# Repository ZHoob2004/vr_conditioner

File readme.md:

# vr_conditioner

__In hingsight, this was a poor choice of chip, and this didn't work - see [mck1117/vr-interface](github.com/mck1117/vr-interface) for working design__

~~VR conditioner board for Honda OBD0, OBD1, and early OBD2 VR sensors~~

~~Based (heavily) on https://rusefi.com/forum/viewtopic.php?f=3&t=1115&p=20857&hilit=honda#p20862~~

~~Rerouted as 2-layer board and reduced PCB area by more than 50%.~~

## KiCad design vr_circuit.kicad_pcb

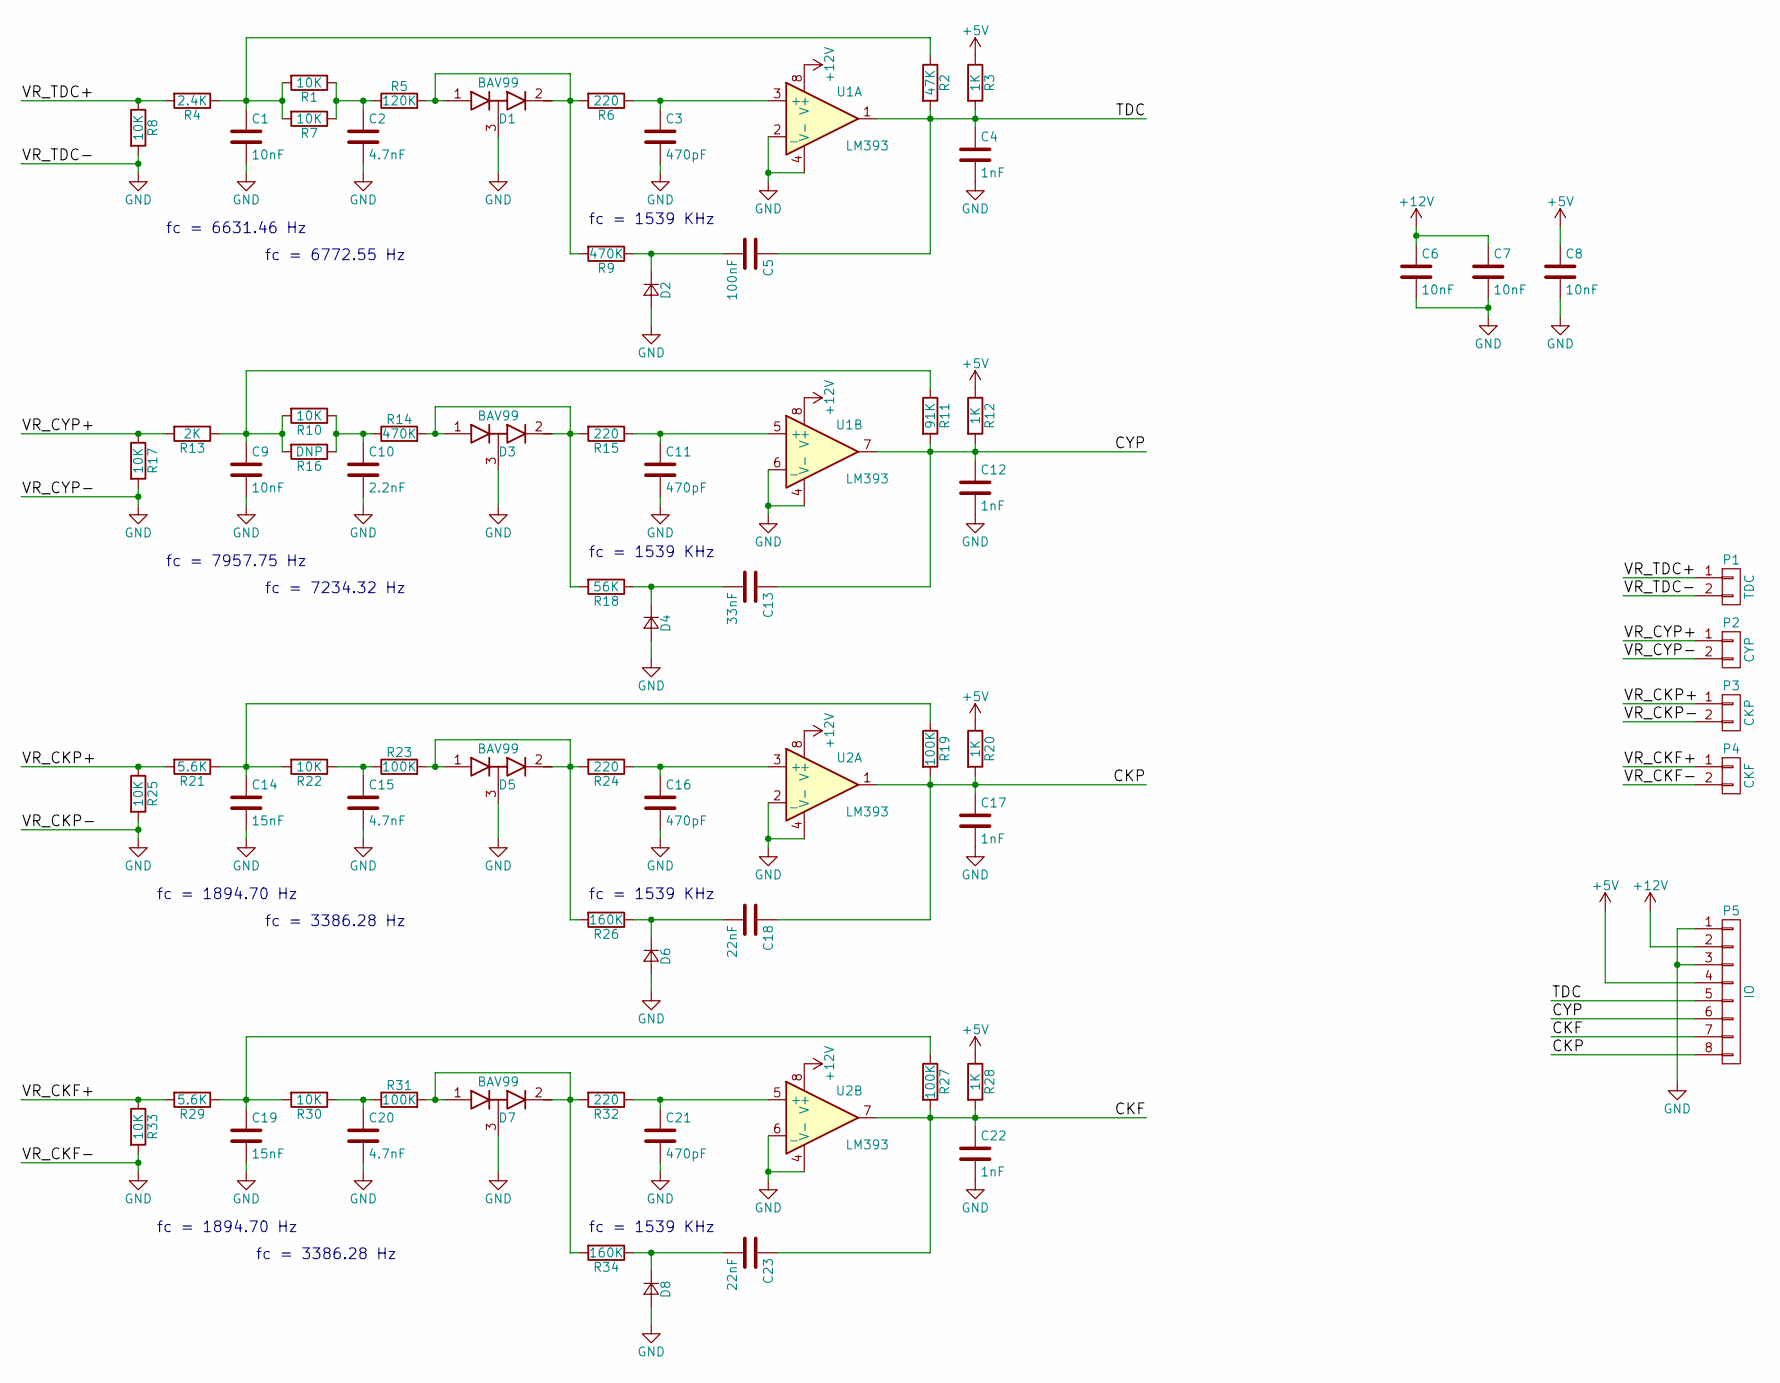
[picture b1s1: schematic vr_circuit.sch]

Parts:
C1, C6, C7, C8, C9: 10nF; C_0805_HandSoldering
C2, C15, C20: 4.7nF; C_0805_HandSoldering
C3, C11, C16, C21: 470pF; C_0805_HandSoldering
C4, C12, C17, C22: 1nF; C_0805_HandSoldering
C5: 100nF; C_1206_HandSoldering
C10: 2.2nF; C_0805_HandSoldering
C13: 33nF; C_1206_HandSoldering
C14, C19: 15nF; C_0805_HandSoldering
C18, C23: 22nF; C_1206_HandSoldering
D1, D3, D5, D7: BAV99; SOT-23_Handsoldering
D2, D4, D6, D8: D_Small; SOD-523
P1: TDC; Pin_Header_Straight_1x02
P2: CYP; Pin_Header_Straight_1x02
P3: CKP; Pin_Header_Straight_1x02
P4: CKF; Pin_Header_Straight_1x02
P5: IO; Pin_Header_Straight_1x08
R1, R7, R10, R22, R30: 10K; R_0805_HandSoldering
R2: 47K; R_0805_HandSoldering
R3, R12, R20, R28: 1K; R_0805_HandSoldering
R4: 2.4K; R_0805_HandSoldering
R5: 120K; R_0805_HandSoldering
R6, R15, R24, R32: 220; R_0805_HandSoldering
R8, R17, R25, R33: 10K; R_2512_HandSoldering
R9, R14: 470K; R_0805_HandSoldering
R11: 91K; R_0805_HandSoldering
R13: 2K; R_0805_HandSoldering
R16: DNP; R_0805_HandSoldering
R18: 56K; R_0805_HandSoldering
R19, R23, R27, R31: 100K; R_0805_HandSoldering
R21, R29: 5.6K; R_0805_HandSoldering
R26, R34: 160K; R_0805_HandSoldering
U1, U2: LM393; SOIC-8-N

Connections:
+5V: C8.1, P5.4, R3.1, R12.1, R20.1, R28.1
+12V: C6.1, C7.1, P5.2, U1.8 (V+), U2.8 (V+)
/CKF: C22.1, C23.1, P5.7, R27.2, R28.2, U2.7
/CKP: C17.1, C18.1, P5.8, R19.2, R20.2, U2.1
/CYP: C12.1, C13.1, P5.6, R11.2, R12.2, U1.7
/TDC: C4.1, C5.1, P5.5, R2.2, R3.2, U1.1
/VR_CKF+: P4.1, R29.2, R33.1
/VR_CKP+: P3.1, R21.2, R25.1
/VR_CYP+: P2.1, R13.2, R17.1
/VR_TDC+: P1.1, R4.2, R8.1
GND: C1.2, C2.2, C3.2, C4.2, C6.2, C7.2, C8.2, C9.2, C10.2, C11.2, C12.2, C14.2, C15.2, C16.2, C17.2, C19.2, C20.2, C21.2, C22.2, D1.3 (common), D2.2 (A), D3.3 (common), D4.2 (A), D5.3 (common), D6.2 (A), D7.3 (common), D8.2 (A), P1.2, P2.2, P3.2, P4.2, P5.1, P5.3, R8.2, R17.2, R25.2, R33.2, U1.2 (_), U1.4 (V-), U1.6 (_), U2.2 (_), U2.4 (V-), U2.6 (_)
unnamed: C1.1, R1.2, R2.1, R4.1, R7.2
unnamed: C2.1, R1.1, R5.1, R7.1
unnamed: C3.1, R6.1, U1.3 (+)
unnamed: C5.2, D2.1 (K), R9.1
unnamed: C9.1, R10.2, R11.1, R13.1, R16.2
unnamed: C10.1, R10.1, R14.1, R16.1
unnamed: C11.1, R15.1, U1.5 (+)
unnamed: C13.2, D4.1 (K), R18.1
unnamed: C14.1, R19.1, R21.1, R22.2
unnamed: C15.1, R22.1, R23.1
unnamed: C16.1, R24.1, U2.3 (+)
unnamed: C18.2, D6.1 (K), R26.1
unnamed: C19.1, R27.1, R29.1, R30.2
unnamed: C20.1, R30.1, R31.1
unnamed: C21.1, R32.1, U2.5 (+)
unnamed: C23.2, D8.1 (K), R34.1
unnamed: D1.1 (A), D1.2 (K), R5.2, R6.2, R9.2
unnamed: D3.1 (A), D3.2 (K), R14.2, R15.2, R18.2
unnamed: D5.1 (A), D5.2 (K), R23.2, R24.2, R26.2
unnamed: D7.1 (A), D7.2 (K), R31.2, R32.2, R34.2

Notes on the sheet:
fc = 6631.46 Hz
fc = 7957.75 Hz
fc = 1894.70 Hz
fc = 7234.32 Hz
fc = 6772.55 Hz
fc = 3386.28 Hz
fc = 1539 KHz

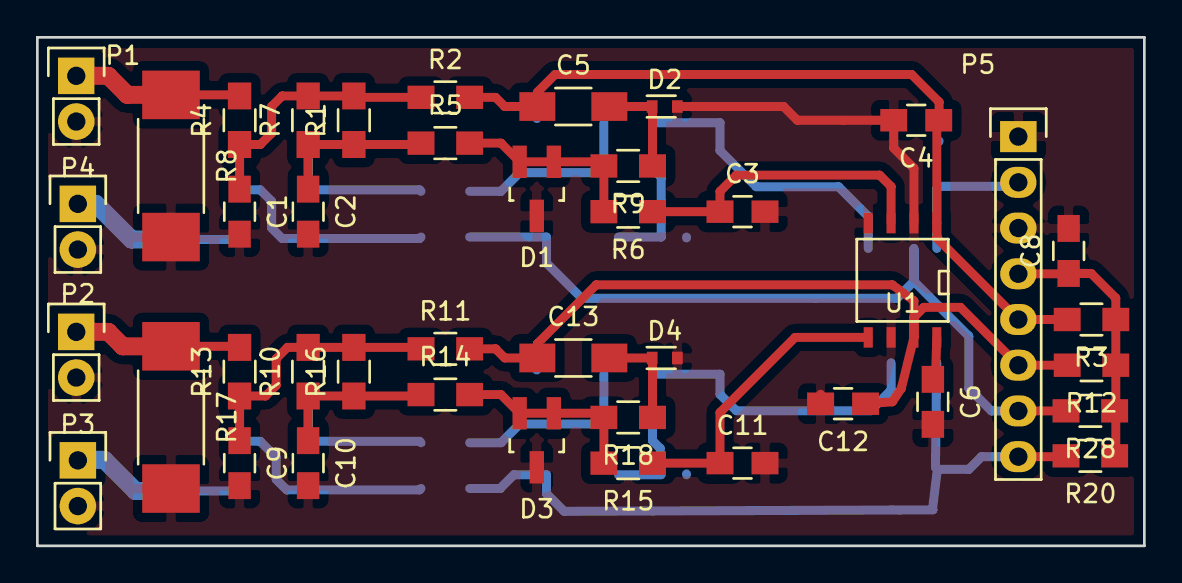
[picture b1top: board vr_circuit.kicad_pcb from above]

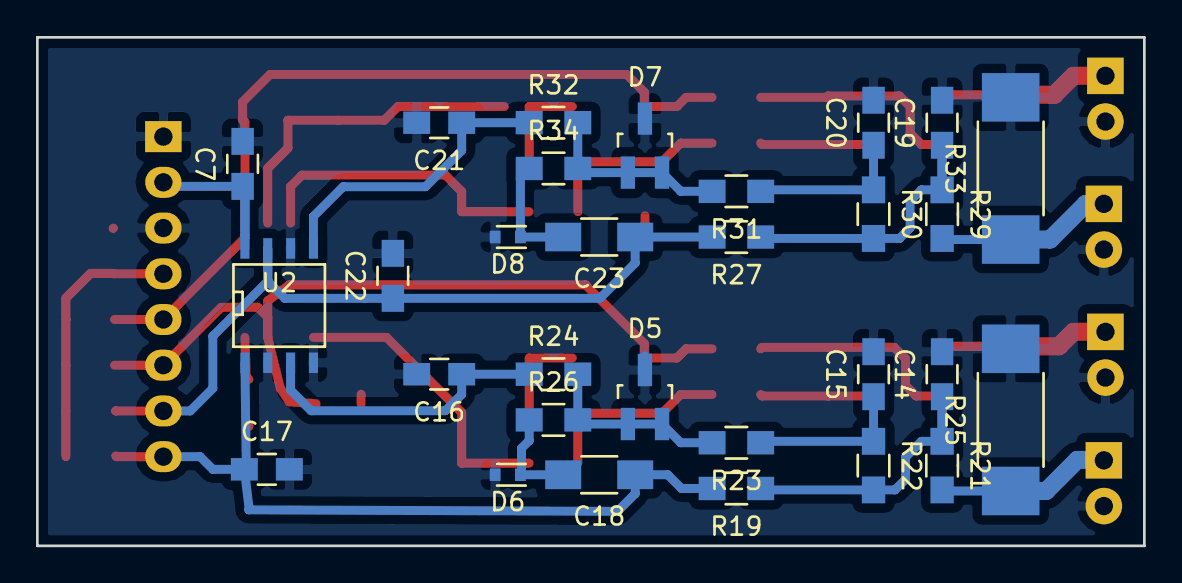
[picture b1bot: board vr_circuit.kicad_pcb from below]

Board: 2 copper layers, 61.5 x 28.2 mm, 72 parts (30 on the bottom side), 31 nets.

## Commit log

2019-01-06 Added readme.md and attribution
